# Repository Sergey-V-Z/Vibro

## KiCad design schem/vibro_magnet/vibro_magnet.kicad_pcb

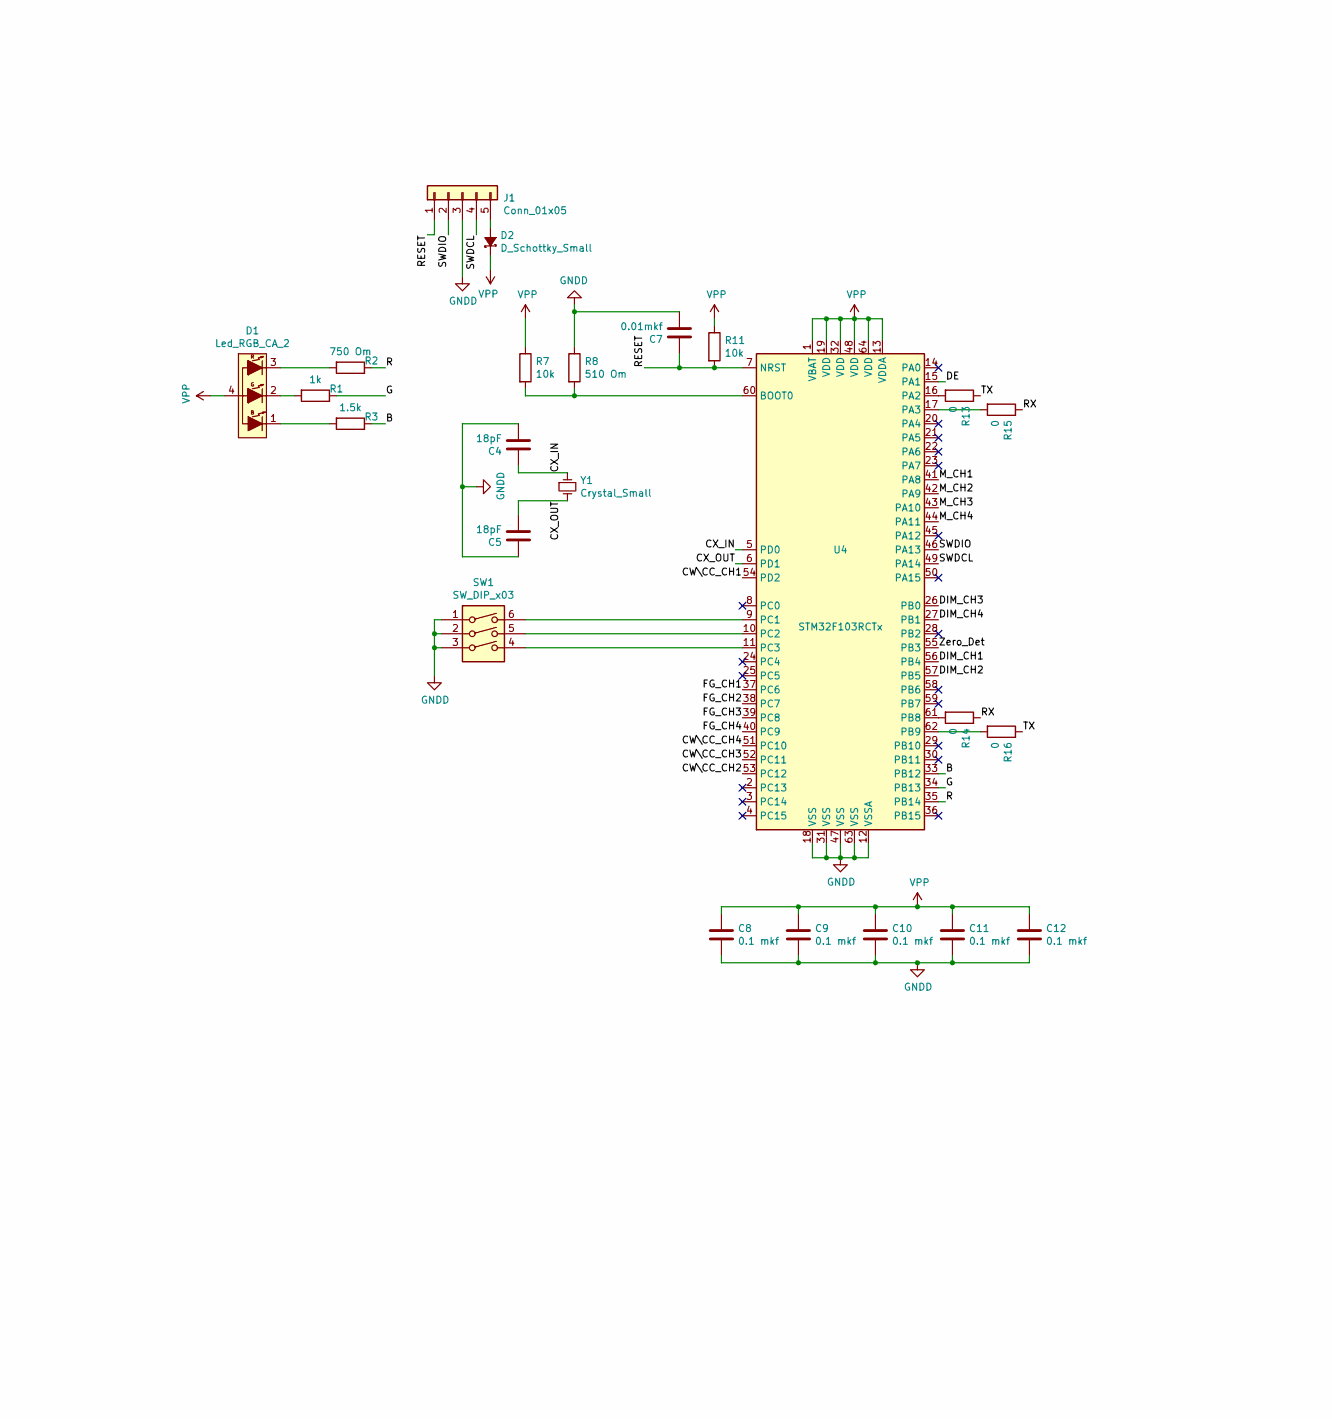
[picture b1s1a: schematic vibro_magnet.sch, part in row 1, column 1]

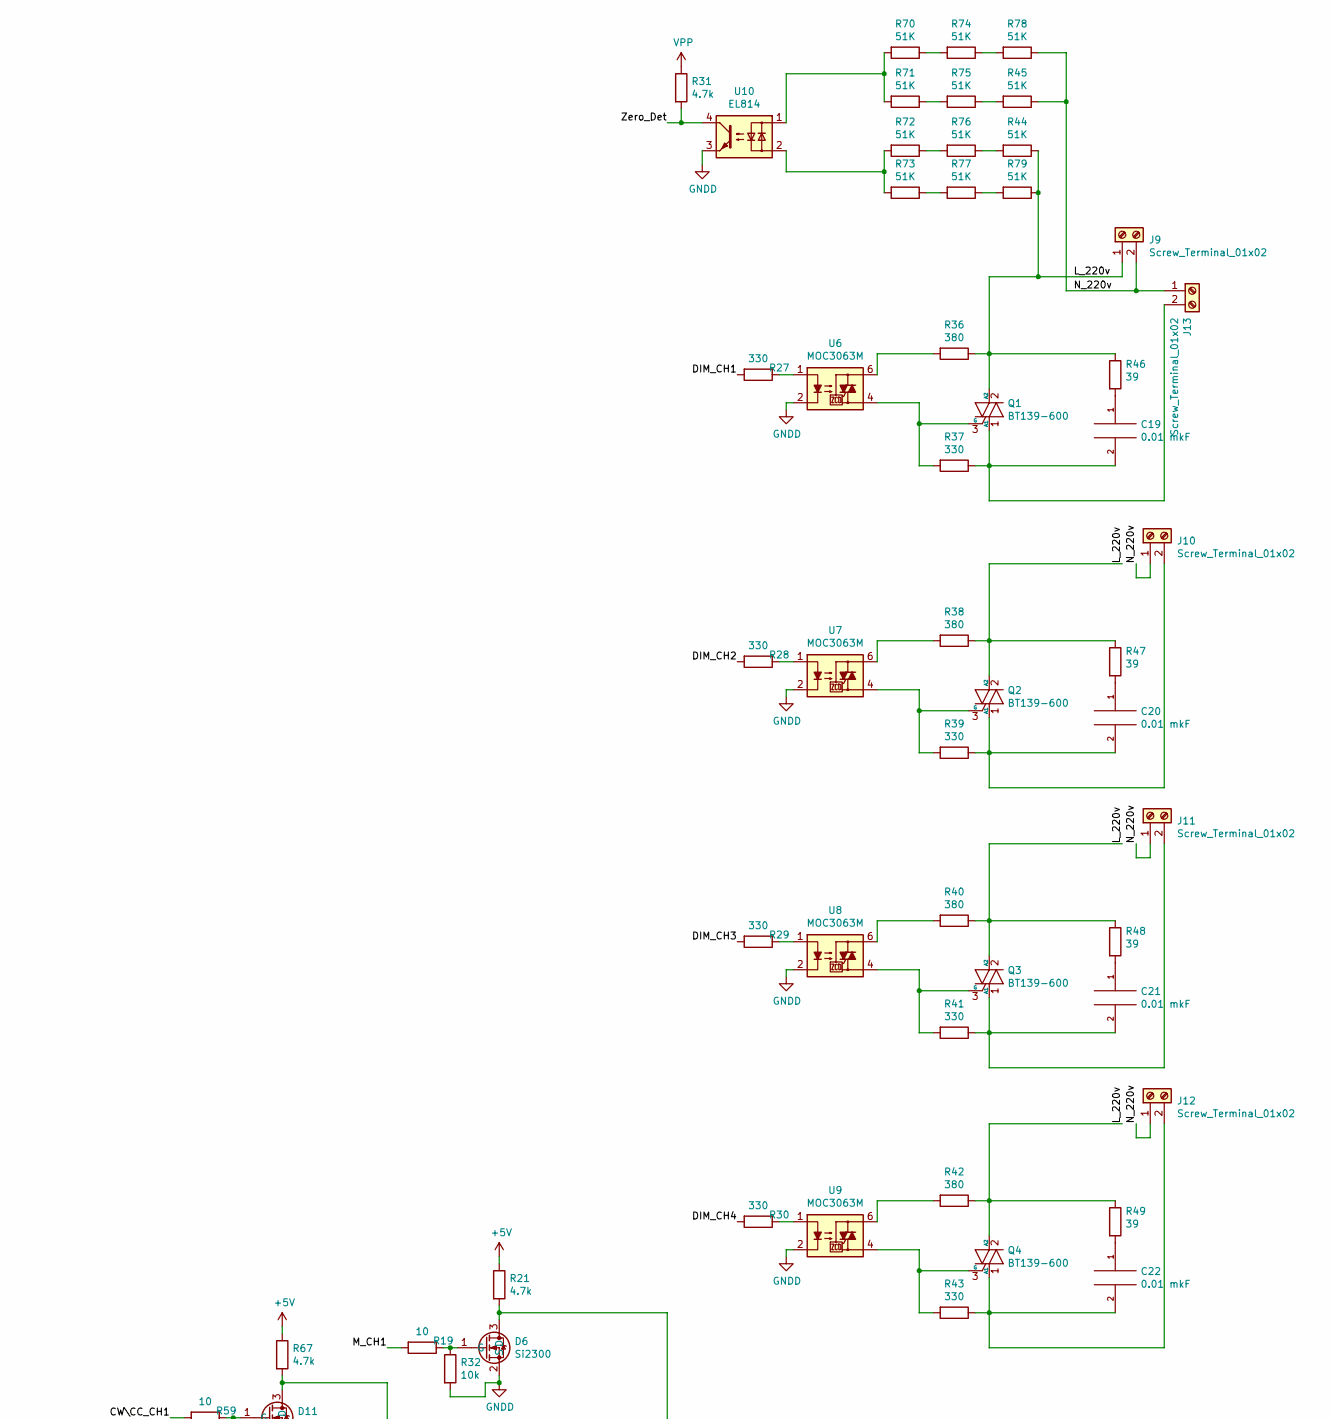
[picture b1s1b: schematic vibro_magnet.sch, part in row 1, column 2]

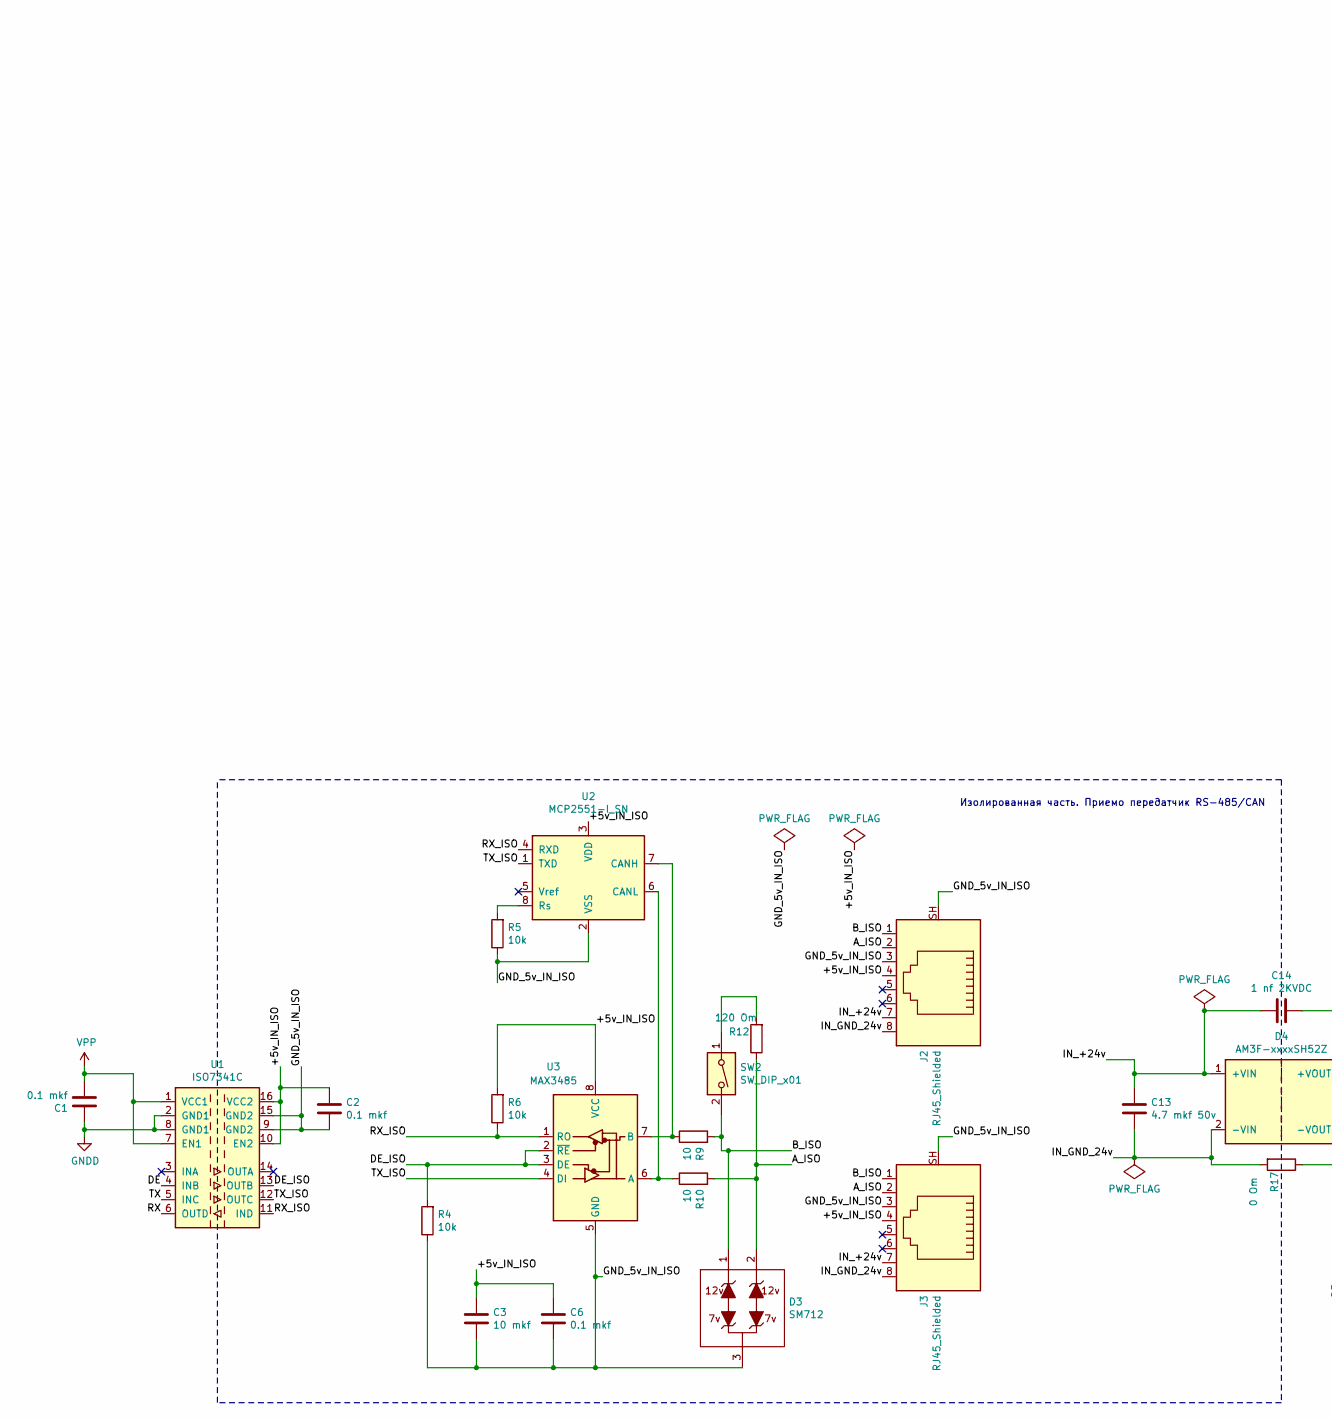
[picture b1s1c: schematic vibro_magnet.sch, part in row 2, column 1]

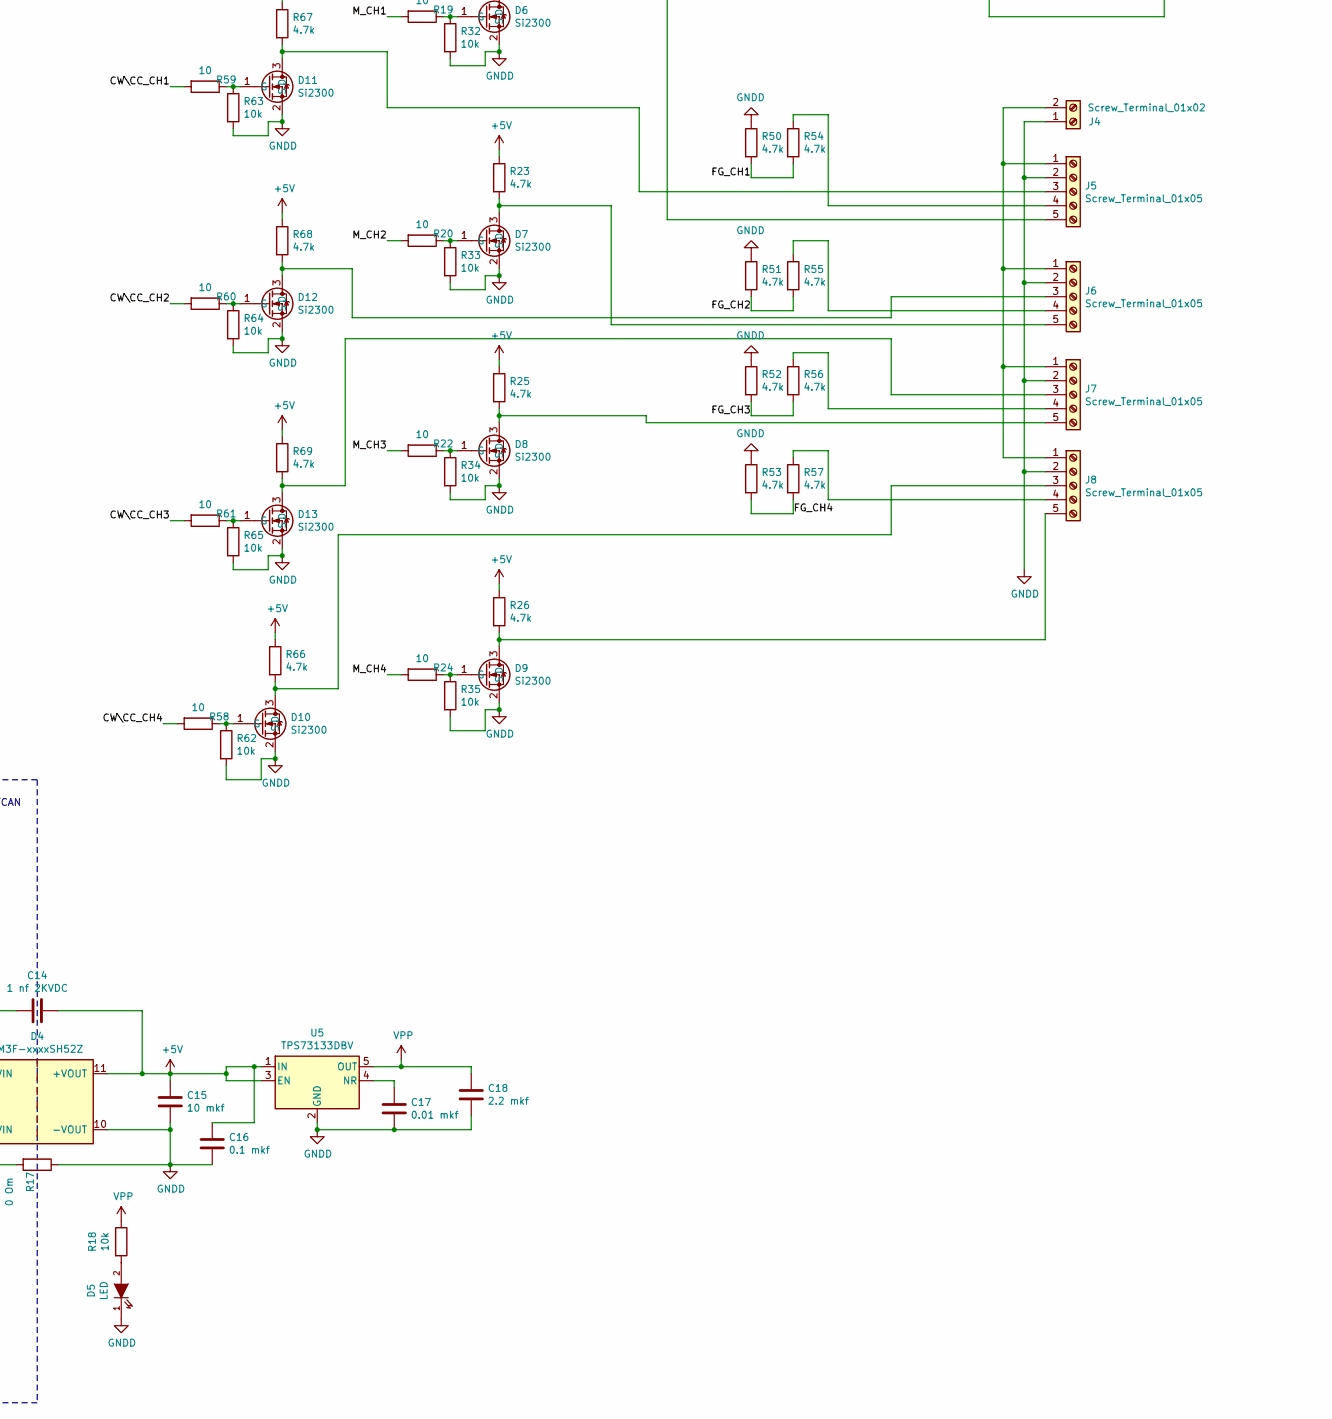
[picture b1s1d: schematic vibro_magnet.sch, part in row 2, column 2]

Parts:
C1, C2, C6, C8, C9, C10, C11, C12: 0.1 mkf; C_0603_1608Metric_Pad1.05x0.95mm_HandSolder
C3, C15: 10 mkf; C_0805_2012Metric_Pad1.15x1.40mm_HandSolder
C4, C5: 18pF; C_0603_1608Metric
C7: 0.01mkf; C_0603_1608Metric_Pad1.05x0.95mm_HandSolder
C13: 4.7 mkf 50v; C_1206_3216Metric_Pad1.42x1.75mm_HandSolder
C14: 1 nf 2KVDC; C_Rect_L7.5mm_W6.5mm_P5.00mm
C16: 0.1 mkf; C_0805_2012Metric_Pad1.15x1.40mm_HandSolder
C17: 0.01 mkf; C_0805_2012Metric_Pad1.15x1.40mm_HandSolder
C18: 2.2 mkf; C_1206_3216Metric
C19, C20, C21, C22: 0.01 mkF; C_Rect_L13.0mm_W5.0mm_P10.00mm_FKS3_FKP3_MKS4
D1: Led_RGB_CA_2; LED_Avago_PLCC4_3.2x2.8mm_CW
D2: D_Schottky_Small; D_SMA-SMB_Universal_Handsoldering
D3: SM712; SOT-23
D4: AM3F-xxxxSH52Z; Converter_DCDC_AM3F-xxxxSH52Z_THT
D5: LED; LED_0805_2012Metric
D6, D7, D8, D9, D10, D11, D12, D13: Si2300; SOT-23
J1: Conn_01x05; PinHeader_1x05_P2.54mm_Vertical
J2, J3: RJ45_Shielded; RJ45_Ninigi_GE
J4, J9, J10, J11, J12, J13: Screw_Terminal_01x02; TerminalBlock_MetzConnect_Type094_RT03502HBLU_1x02_P5.00mm_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
J5, J6, J7, J8: Screw_Terminal_01x05; TerminalBlock_MetzConnect_Type094_RT03505HBLU_1x05_P5.00mm_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
Q1, Q2, Q3, Q4: BT139-600; TO-220-3_Vertical
R1: 1k; R_0805_2012Metric_Pad1.15x1.40mm_HandSolder
R2: 750 Om; R_0805_2012Metric_Pad1.15x1.40mm_HandSolder
R3: 1.5k; R_0805_2012Metric_Pad1.15x1.40mm_HandSolder
R4, R5, R6, R7, R11, R18, R32, R33, R34, R35, R62, R63, R64, R65: 10k; R_0805_2012Metric_Pad1.15x1.40mm_HandSolder
R8: 510 Om; R_0805_2012Metric_Pad1.15x1.40mm_HandSolder
R9, R10, R19, R20, R22, R24, R58, R59, R60, R61: 10; R_0805_2012Metric_Pad1.15x1.40mm_HandSolder
R12: 120 Om; R_0805_2012Metric_Pad1.15x1.40mm_HandSolder
R13, R14, R15, R16: 0; R_0805_2012Metric_Pad1.15x1.40mm_HandSolder
R17: 0 Om; R_1206_3216Metric_Pad1.42x1.75mm_HandSolder
R21, R23, R25, R26, R31, R50, R51, R52, R53, R54, R55, R56, R57, R66, R67, R68, R69: 4.7k; R_0805_2012Metric_Pad1.15x1.40mm_HandSolder
R27, R28, R29, R30, R37, R39, R41, R43: 330; R_0805_2012Metric_Pad1.15x1.40mm_HandSolder
R36, R38, R40, R42: 380; R_0805_2012Metric_Pad1.15x1.40mm_HandSolder
R44, R45, R71, R72, R75, R76: 51K; R_0805_2012Metric_Pad1.15x1.40mm_HandSolder
R46, R47, R48, R49: 39; R_Axial_DIN0516_L15.5mm_D5.0mm_P20.32mm_Horizontal
R70, R73, R74, R77, R78, R79: 51K; R_1206_3216Metric
SW1: SW_DIP_x03; SW_DIP_SPSTx03_Slide_9.78x9.8mm_W7.62mm_P2.54mm
SW2: SW_DIP_x01; SW_DIP_SPSTx01_Slide_9.78x4.72mm_W7.62mm_P2.54mm
U1: ISO7341C; SOIC-16W_7.5x10.3mm_P1.27mm
U2: MCP2551-I_SN; SO-8_3.9x4.9mm_P1.27mm
U3: MAX3485; SOIC-8_3.9x4.9mm_P1.27mm
U4: STM32F103RCTx; LQFP-64_10x10mm_P0.5mm
U5: TPS73133DBV; SOT-23-5
U6, U7, U8, U9: MOC3063M; DIP-6_W7.62mm_LongPads
U10: EL814; DIP-4_W7.62mm_LongPads
Y1: Crystal_Small; Crystal_SMD_HC49-SD

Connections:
+5V: C14.1, C15.1, C16.1, D4.11 (+VOUT), R21.1, R23.1, R25.1, R26.1, R66.1, R67.1, R68.1, R69.1, U5.1 (IN), U5.3 (EN)
/+5v_IN_ISO: C2.1, C3.1, C6.1, J2.4, J3.4, R6.2, U1.10 (EN2), U1.16 (VCC2), U2.3 (VDD), U3.8 (VCC)
/A_ISO: D3.2, J2.2, J3.2, R10.2, R12.1
/B: R3.1, U4.33 (PB12)
/B_ISO: D3.1, J2.1, J3.1, R9.2, SW2.2
/CW\CC_CH1: R59.2, U4.54 (PD2)
/CW\CC_CH2: R60.2, U4.53 (PC12)
/CW\CC_CH3: R61.2, U4.52 (PC11)
/CW\CC_CH4: R58.2, U4.51 (PC10)
/CX_IN: C4.1, U4.5 (PD0), Y1.1
/CX_OUT: C5.2, U4.6 (PD1), Y1.2
/DE: U1.4 (INB), U4.15 (PA1)
/DE_ISO: R4.2, U1.13 (OUTB), U3.2 (~RE), U3.3 (DE)
/DIM_CH1: R27.2, U4.56 (PB4)
/DIM_CH2: R28.2, U4.57 (PB5)
/DIM_CH3: R29.2, U4.26 (PB0)
/DIM_CH4: R30.2, U4.27 (PB1)
/FG_CH1: R50.2, R54.2, U4.37 (PC6)
/FG_CH2: R51.2, R55.2, U4.38 (PC7)
/FG_CH3: R52.2, R56.2, U4.39 (PC8)
/FG_CH4: R53.2, R57.2, U4.40 (PC9)
/G: R1.1, U4.34 (PB13)
/GND_5v_IN_ISO: C2.2, C3.2, C6.2, D3.3, J2.3, J2.SH, J3.3, J3.SH, R4.1, R5.1, U1.9 (GND2), U1.15 (GND2), U2.2 (VSS), U3.5 (GND)
/IN_+24v: C13.1, C14.2, D4.1 (+VIN), J2.7, J3.7
/IN_GND_24v: C13.2, D4.2 (-VIN), J2.8, J3.8, R17.2
/L_220v: J9.1, Q1.2 (A2), Q2.2 (A2), Q3.2 (A2), Q4.2 (A2), R36.1, R38.1, R40.1, R42.1, R44.1, R46.1, R47.1, R48.1, R49.1, R79.1
/M_CH1: R19.2, U4.41 (PA8)
/M_CH2: R20.2, U4.42 (PA9)
/M_CH3: R22.2, U4.43 (PA10)
/M_CH4: R24.2, U4.44 (PA11)
/N_220v: J9.2, J10.1, J11.1, J12.1, J13.1, R45.1, R78.1
/R: R2.1, U4.35 (PB14)
/RESET: C7.1, J1.1, R11.2, U4.7 (NRST)
/RX: R14.1, R15.1, U1.6 (OUTD)
/RX_ISO: R6.1, U1.11 (IND), U2.4 (RXD), U3.1 (RO)
/SWDCL: J1.4, U4.49 (PA14)
/SWDIO: J1.2, U4.46 (PA13)
/TX: R13.1, R16.1, U1.5 (INC)
/TX_ISO: U1.12 (OUTC), U2.1 (TXD), U3.4 (DI)
/Zero_Det: R31.2, U4.55 (PB3), U10.4
GNDD: C1.1, C4.2, C5.1, C7.2, C8.2, C9.2, C10.2, C11.2, C12.2, C15.2, C16.2, C17.2, C18.2, D4.10 (-VOUT), D5.1 (K), D6.2 (S), D7.2 (S), D8.2 (S), D9.2 (S), D10.2 (S), D11.2 (S), D12.2 (S), D13.2 (S), J1.3, J4.1, J5.2, J6.2, J7.2, J8.2, R8.1, R17.1, R32.2, R33.2, R34.2, R35.2, R50.1, R51.1, R52.1, R53.1, R62.2, R63.2, R64.2, R65.2, SW1.1, SW1.2, SW1.3, U1.2 (GND1), U1.8 (GND1), U4.12 (VSSA), U4.18 (VSS), U4.31 (VSS), U4.47 (VSS), U4.63 (VSS), U5.2 (GND), U6.2, U7.2, U8.2, U9.2, U10.3
unnamed: C17.1, U5.4 (NR)
unnamed: C19.1, R46.2
unnamed: C19.2, J13.2, Q1.1 (A1), R37.1
unnamed: C20.1, R47.2
unnamed: C20.2, J10.2, Q2.1 (A1), R39.1
unnamed: C21.1, R48.2
unnamed: C21.2, J11.2, Q3.1 (A1), R41.1
unnamed: C22.1, R49.2
unnamed: C22.2, J12.2, Q4.1 (A1), R43.1
unnamed: D1.1 (B), R3.2
unnamed: D1.2 (G), R1.2
unnamed: D1.3 (R), R2.2
unnamed: D2.2 (A), J1.5
unnamed: D5.2 (A), R18.2
unnamed: D6.1 (G), R19.1, R32.1
unnamed: D6.3 (D), J5.5, R21.2
unnamed: D7.1 (G), R20.1, R33.1
unnamed: D7.3 (D), J6.5, R23.2
unnamed: D8.1 (G), R22.1, R34.1
unnamed: D8.3 (D), J7.5, R25.2
unnamed: D9.1 (G), R24.1, R35.1
unnamed: D9.3 (D), J8.5, R26.2
unnamed: D10.1 (G), R58.1, R62.1
unnamed: D10.3 (D), J8.3, R66.2
unnamed: D11.1 (G), R59.1, R63.1
unnamed: D11.3 (D), J5.3, R67.2
unnamed: D12.1 (G), R60.1, R64.1
unnamed: D12.3 (D), J6.3, R68.2
unnamed: D13.1 (G), R61.1, R65.1
unnamed: D13.3 (D), J7.3, R69.2
unnamed: J4.2, J5.1, J6.1, J7.1, J8.1
unnamed: J5.4, R54.1
unnamed: J6.4, R55.1
unnamed: J7.4, R56.1
unnamed: J8.4, R57.1
unnamed: Q1.3 (G), R37.2, U6.4
unnamed: Q2.3 (G), R39.2, U7.4
unnamed: Q3.3 (G), R41.2, U8.4
unnamed: Q4.3 (G), R43.2, U9.4
unnamed: R5.2, U2.8 (Rs)
unnamed: R7.2, R8.2, U4.60 (BOOT0)
unnamed: R9.1, U2.7 (CANH), U3.7 (B)
unnamed: R10.1, U2.6 (CANL), U3.6 (A)
unnamed: R12.2, SW2.1
unnamed: R13.2, U4.16 (PA2)
unnamed: R14.2, U4.61 (PB8)
unnamed: R15.2, U4.17 (PA3)
unnamed: R16.2, U4.62 (PB9)
unnamed: R27.1, U6.1
unnamed: R28.1, U7.1
unnamed: R29.1, U8.1
unnamed: R30.1, U9.1
unnamed: R36.2, U6.6
unnamed: R38.2, U7.6
unnamed: R40.2, U8.6
unnamed: R42.2, U9.6
unnamed: R44.2, R76.1
unnamed: R45.2, R75.1
unnamed: R70.1, R74.2
unnamed: R70.2, R71.2, U10.1
unnamed: R71.1, R75.2
unnamed: R72.1, R76.2
unnamed: R72.2, R73.2, U10.2
unnamed: R73.1, R77.2
unnamed: R74.1, R78.2
unnamed: R77.1, R79.2
unnamed: SW1.4, U4.11 (PC3)
unnamed: SW1.5, U4.10 (PC2)
unnamed: SW1.6, U4.9 (PC1)
VPP: C1.2, C8.1, C9.1, C10.1, C11.1, C12.1, C18.1, D1.4, D2.1 (K), R7.1, R11.1, R18.1, R31.1, U1.1 (VCC1), U1.7 (EN1), U4.1 (VBAT), U4.13 (VDDA), U4.19 (VDD), U4.32 (VDD), U4.48 (VDD), U4.64 (VDD), U5.5 (OUT)

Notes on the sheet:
Изолированная часть. Приемо передатчик RS-485/CAN

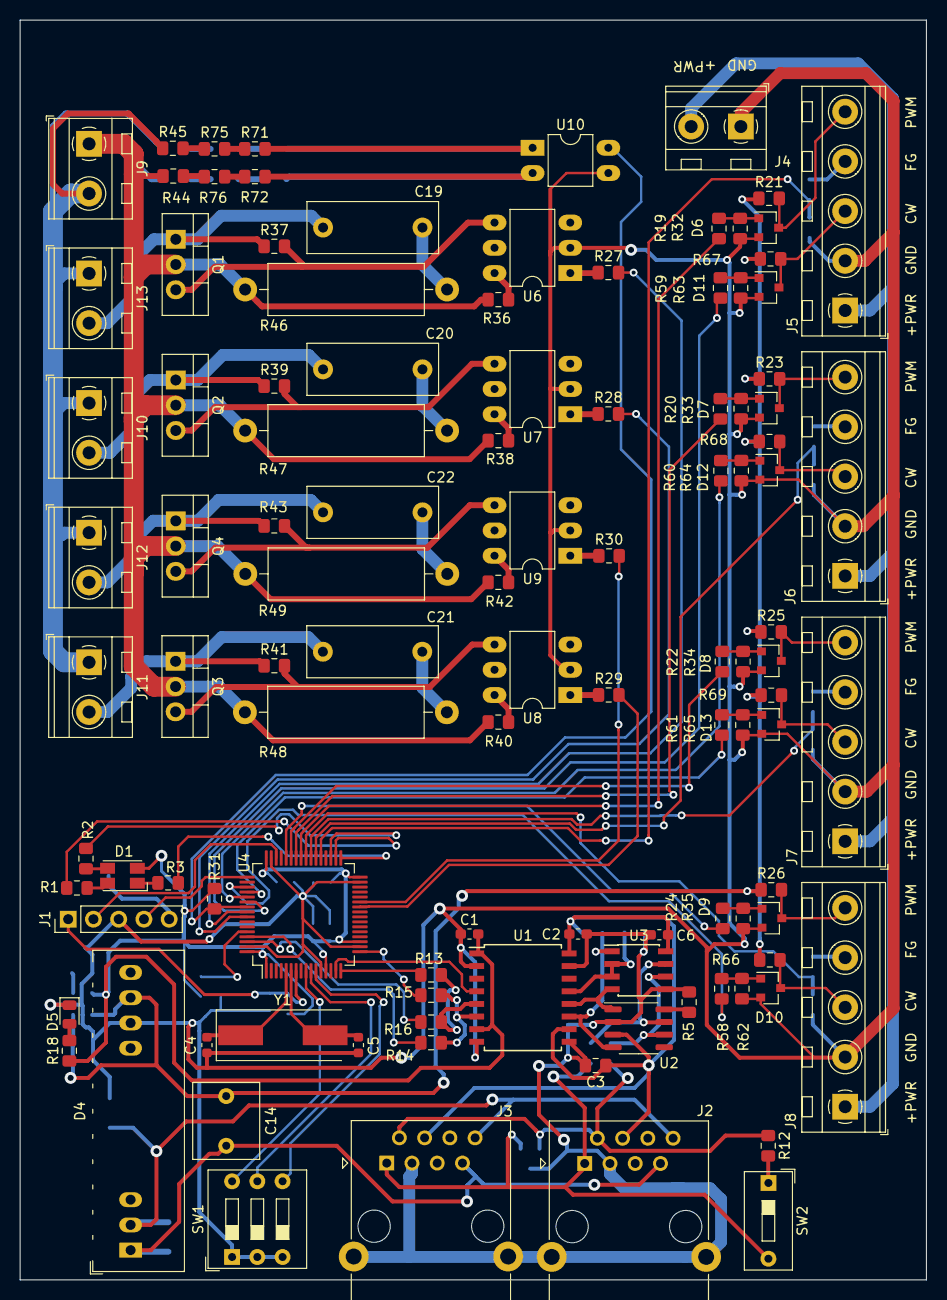
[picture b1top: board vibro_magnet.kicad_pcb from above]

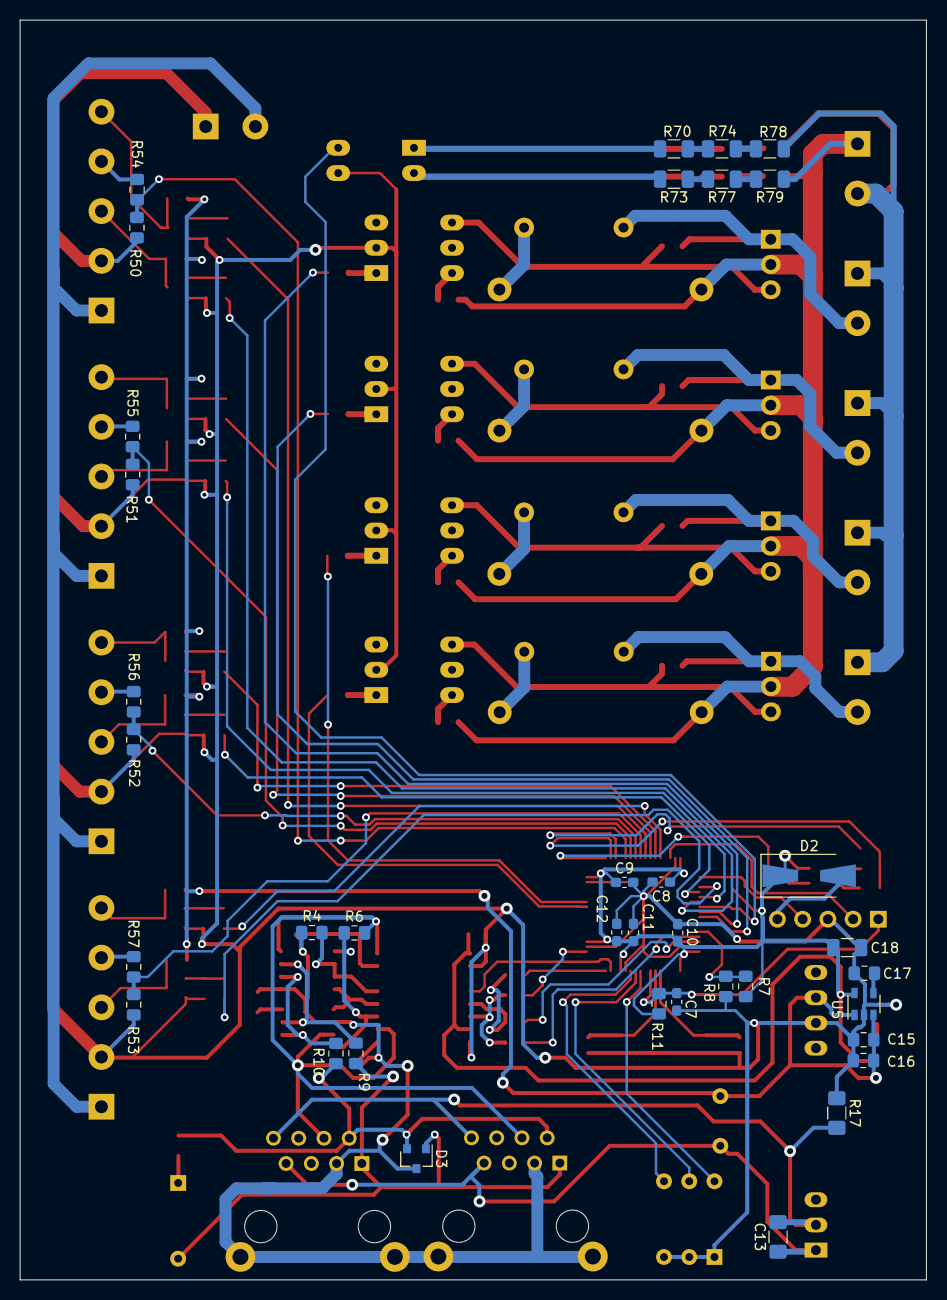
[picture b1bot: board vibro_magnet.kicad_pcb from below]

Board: 2 copper layers, 91.2 x 126.7 mm, 144 parts (36 on the bottom side), 111 nets.

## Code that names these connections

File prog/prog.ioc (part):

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Mcu.Name=STM32F103R(C-D-E)Tx
Mcu.Package=LQFP64
Mcu.UserName=STM32F103RCTx
PA1.GPIOParameters=GPIO_Speed,GPIO_Label
PA1.GPIO_Label=RS485_1_Rs
PA1.GPIO_Speed=GPIO_SPEED_FREQ_HIGH
PA1.Signal=GPIO_Output
PA13.Mode=Serial_Wire
PA13.Signal=SYS_JTMS-SWDIO
PA14.Mode=Serial_Wire
PA14.Signal=SYS_JTCK-SWCLK
PA2.Mode=Asynchronous
PA2.Signal=USART2_TX
PA3.Mode=Asynchronous
PA3.Signal=USART2_RX
PB0.Signal=S_TIM3_CH3
PB1.Signal=S_TIM3_CH4
PB12.GPIOParameters=GPIO_Speed,PinState,GPIO_Label
PB12.GPIO_Label=B
PB12.GPIO_Speed=GPIO_SPEED_FREQ_LOW
PB12.PinState=GPIO_PIN_SET
PB12.Signal=GPIO_Output
PB13.GPIOParameters=GPIO_Speed,PinState,GPIO_Label
PB13.GPIO_Label=G
PB13.GPIO_Speed=GPIO_SPEED_FREQ_LOW
PB13.PinState=GPIO_PIN_SET
PB13.Signal=GPIO_Output
PB14.GPIOParameters=GPIO_Speed,PinState,GPIO_Label
PB14.GPIO_Label=R
PB14.GPIO_Speed=GPIO_SPEED_FREQ_LOW
PB14.PinState=GPIO_PIN_SET
PB14.Signal=GPIO_Output
PB3.GPIOParameters=GPIO_Label,GPIO_ModeDefaultEXTI
PB3.GPIO_Label=Neg
PB3.GPIO_ModeDefaultEXTI=GPIO_MODE_IT_FALLING
PB3.Signal=GPXTI3
PB4.Signal=S_TIM3_CH1
PB5.Signal=S_TIM3_CH2
PB8.Mode=Master
PB8.Signal=CAN_RX
PB9.Mode=Master
PB9.Signal=CAN_TX
PC1.Signal=GPIO_Input
PC2.Signal=GPIO_Input
PC3.Signal=GPIO_Input
PC6.GPIOParameters=GPIO_PuPd,GPIO_Label,GPIO_ModeDefaultEXTI
PC6.GPIO_Label=Pos
PC6.GPIO_ModeDefaultEXTI=GPIO_MODE_IT_FALLING
PC6.GPIO_PuPd=GPIO_PULLUP
PC6.Signal=GPXTI6
PD0-OSC_IN.Mode=HSE-External-Oscillator
PD0-OSC_IN.Signal=RCC_OSC_IN
PD1-OSC_OUT.Mode=HSE-External-Oscillator
PD1-OSC_OUT.Signal=RCC_OSC_OUT
RCC.HSEDivPLL=RCC_HSE_PREDIV_DIV2
RCC.HSE_VALUE=10000000
RCC.SYSCLKFreq_VALUE=70000000
RCC.SYSCLKSource=RCC_SYSCLKSOURCE_PLLCLK
board=custom

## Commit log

2020-07-14 Первый
2020-07-15 Добавлен ModBus. Сделана начальная настрока
2020-07-18 в процессе написания логики работы устройсва
2020-07-19 Реализация сохранение настроек во флешь
2020-07-19 Отлажена Запись во Flash
2020-07-20 Диммирование переделано на аппаратную часть(таймер) . В ModBus добавлены регистры для управления каналами.
2020-07-23 first finish
2020-10-31 Half mode
    Добавление "режима пол синусоиды"
